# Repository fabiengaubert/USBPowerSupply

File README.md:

# USBPowerSupply

USB Power supply design for eurorack, works with powerbanks or good USB wallwarts

- 2 HP
- 500mA at +12v, 500mA at - 12v
- efficient isolated DC-DC switching regulators with low heat release
- surge voltage and over-current protection with resettable fuse
- reversed polarity protection
- common mode choke and multiple ferrite beads with PI filters for noise filtering
- 1 LED per rail to indicated overload and short circuits

Warning and reserves:
- the two DC-DC switching regulators are expensive compared to the rest of the components: they represent about 75% of the total cost, I will work on a cheaper version with at least the same performances in the future
- the minimum voltage allowed is 4.5v, which we know can be too much for USB chargers, as they are unregulated sources of voltage. when current rises above 0.5A, most of them drop the voltage below this value. There is a need to test chargers and advise specific ones. With power banks they should be no problems as their output is regulated

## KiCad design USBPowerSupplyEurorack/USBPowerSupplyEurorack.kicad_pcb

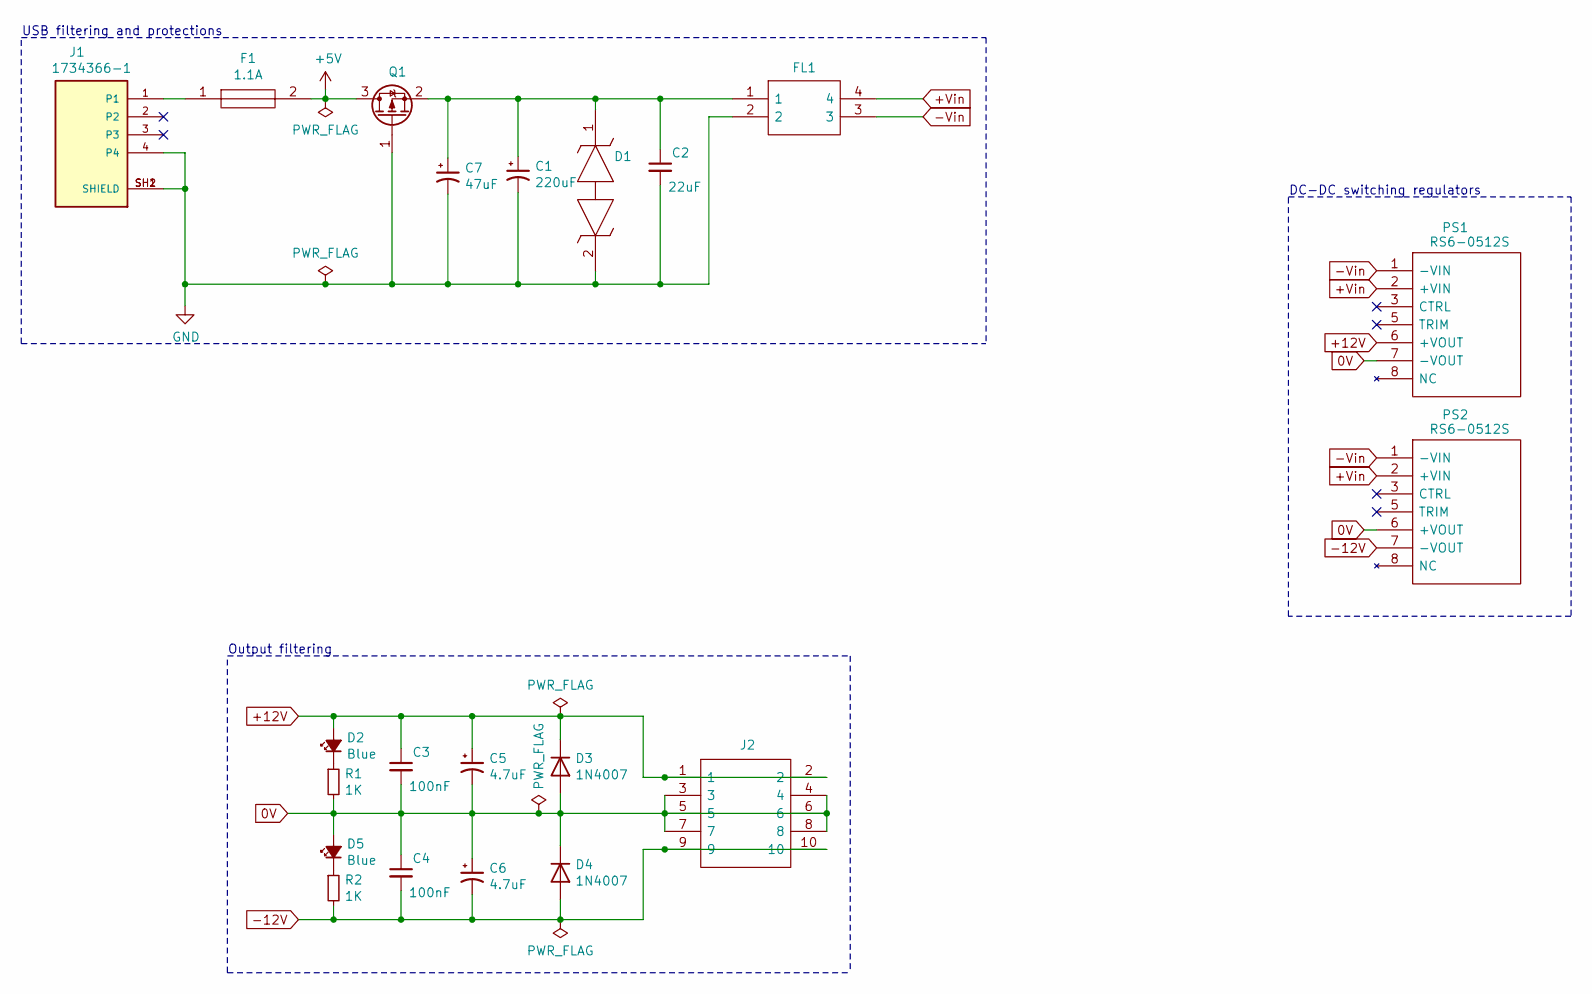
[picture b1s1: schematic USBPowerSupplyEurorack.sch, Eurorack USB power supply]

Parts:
C1: 220uF; C_Elec_6.3x7.7; LCSC C127327
C2: 22uF; C_0805_2012Metric; LCSC C45783
C3, C4: 100nF; C_0402_1005Metric; LCSC C1525
C5, C6: 4.7uF; C_Elec_4x5.4; LCSC C116398
C7: 47uF; C_Elec_5x5.4; LCSC C294514
D1: SMAJ5.0CA; DO-214AC-BIPOLAR; Manufacturer_Part_Number SMAJ5.0CA; Mouser Part Number 576-SMAJ5.0CA
D2, D5: Blue; LED_0603
D3, D4: 1N4007; D_SOD-123F; LCSC C64898
F1: 1.1A; Fuse_1812_4532Metric; Manufacturer_Part_Number 1812L110/16DR; Mouser Part Number 576-1812L110/16DR
FL1: ACP3225-102-2P-T000; ACP3225; Manufacturer_Part_Number ACP3225-102-2P-T000; Mouser Part Number 810-ACP32251022PT000
J1: 1734366-1; TE_1734366-1
J2: 95278-501A10LF; 95278501A10LF; Manufacturer_Part_Number 95278-501A10LF; Mouser Part Number 649-95278-501A10LF
PS1, PS2: RS6-0512S; RS60512S; Manufacturer_Part_Number RS6-0512S; Mouser Part Number 919-RS6-0512S
Q1: Q_PMOS_GSD; SOT-23-3; LCSC C15127
R1, R2: 1K; R_0805_2012Metric; LCSC C17513

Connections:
0V: C3.2, C4.1, C5.2, C6.1, D3.2 (A), D4.1 (K), D5.2 (A), J2.3, J2.4, J2.5, J2.6, J2.7, J2.8, PS1.7 (-VOUT), PS2.6 (+VOUT), R1.2
+5V: F1.2, Q1.3 (D)
+12V: C3.1, C5.1, D2.2 (A), D3.1 (K), J2.1, J2.2, PS1.6 (+VOUT)
+Vin: FL1.4, PS1.2 (+VIN), PS2.2 (+VIN)
-12V: C4.2, C6.2, D4.2 (A), J2.9, J2.10, PS2.7 (-VOUT), R2.2
-Vin: FL1.3, PS1.1 (-VIN), PS2.1 (-VIN)
GND: C1.2, C2.2, C7.2, D1.2, FL1.2, J1.4, J1.SH1 (SHIELD), J1.SH2 (SHIELD), Q1.1 (G)
unnamed: C1.1, C2.1, C7.1, D1.1, FL1.1, Q1.2 (S)
unnamed: D2.1 (K), R1.1
unnamed: D5.1 (K), R2.1
unnamed: F1.1, J1.1

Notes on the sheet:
USB filtering and protections
DC-DC switching regulators
Output filtering

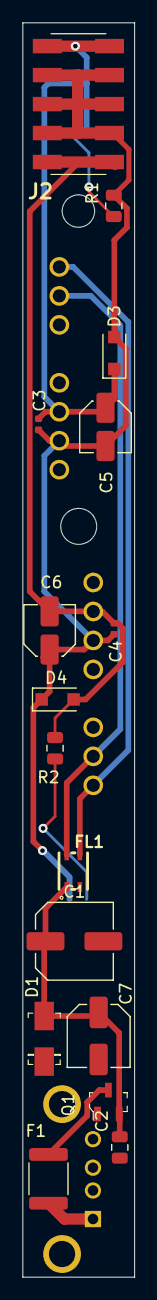
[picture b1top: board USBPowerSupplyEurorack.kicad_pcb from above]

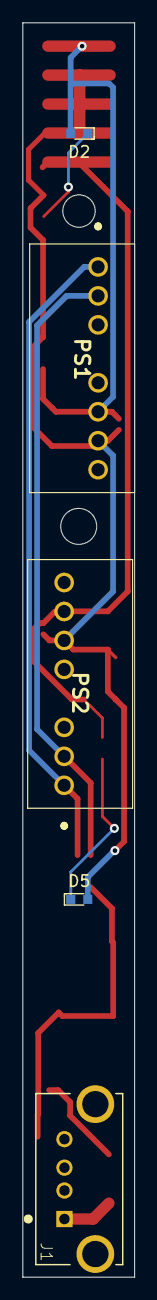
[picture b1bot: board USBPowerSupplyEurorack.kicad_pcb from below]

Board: 2 copper layers, 9.8 x 110.0 mm, 21 parts (5 on the bottom side), 11 nets.

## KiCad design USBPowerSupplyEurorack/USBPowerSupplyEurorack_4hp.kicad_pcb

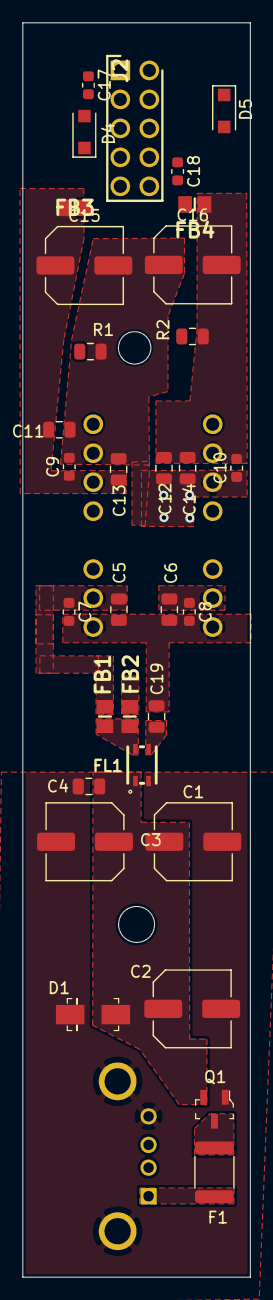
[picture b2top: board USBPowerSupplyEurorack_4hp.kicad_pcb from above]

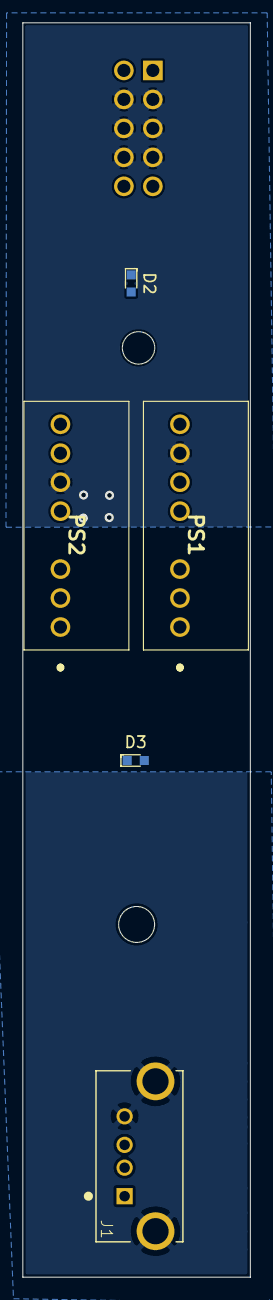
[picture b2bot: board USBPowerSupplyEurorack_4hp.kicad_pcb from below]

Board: 2 copper layers, 19.9 x 110.0 mm, 37 parts (5 on the bottom side), 16 nets, no tracks yet.

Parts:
C1, C15, C16: 47uF; C_Elec_6.3x5.4
C2, C3: 220uF; C_Elec_6.3x7.7
C4, C5, C6, C11, C12, C13, C14: 22uF; C_0805_2012Metric
C7, C8, C9, C10, C17, C18: 100nF; C_0603_1608Metric
C19: 10uF; C_0805_2012Metric
D1: SMAJ5.0CA; DO-214AC-BIPOLAR
D2, D3: Blue; LED_0603
D4, D5: 1N4007; D_SOD-123F
F1: 3A hold; Fuse_1812_4532Metric
FB1, FB2, FB3, FB4: C15957; BEADC2012X105N
FL1: ACP3225-102-2P-T000; ACP3225
J1: 1734366-1; TE_1734366-1
J2: 10129381-910001BLF; HDRV10W67P254_2X5_1270X483X858P
PS1, PS2: RS6-0512S; RS60512S
Q1: Q_PMOS_GSD; SOT-23-3
R1, R2: 1K; R_0805_2012Metric

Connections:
0V: C9.2, C10.1, C11.2, C12.1, C13.2, C14.1, C15.2, C16.1, C17.2, C18.1, D3.2, D4.2, D5.1, J2.3, J2.4, J2.5, J2.6, J2.7, J2.8, PS1.7, PS2.6, R1.2
+5V: F1.2, Q1.3
+12V: C9.1, C11.1, C13.1, C15.1, D2.2, FB3.2, PS1.6
+Vin1: C5.1, C7.1, FB1.1, PS1.2
+Vin2: C6.1, C8.1, FB2.1, PS2.2
-12V: C10.2, C12.2, C14.2, C16.2, FB4.2, PS2.7, R2.2
-Vin1: C5.2, C6.2, C7.2, C8.2, C19.2, PS1.1, PS2.1
GND: C1.2, C2.2, C3.2, C4.2, D1.2, FL1.2, J1.4, J1.SH1, J1.SH2, Q1.1
unnamed: C1.1, C2.1, C3.1, C4.1, D1.1, FL1.1, Q1.2
unnamed: C17.1, D4.1, FB3.1, J2.1, J2.2
unnamed: C18.2, D5.2, FB4.1, J2.9, J2.10
unnamed: C19.1, FL1.3
unnamed: D2.1, R1.1
unnamed: D3.1, R2.1
unnamed: F1.1, J1.1
unnamed: FB1.2, FB2.2, FL1.4

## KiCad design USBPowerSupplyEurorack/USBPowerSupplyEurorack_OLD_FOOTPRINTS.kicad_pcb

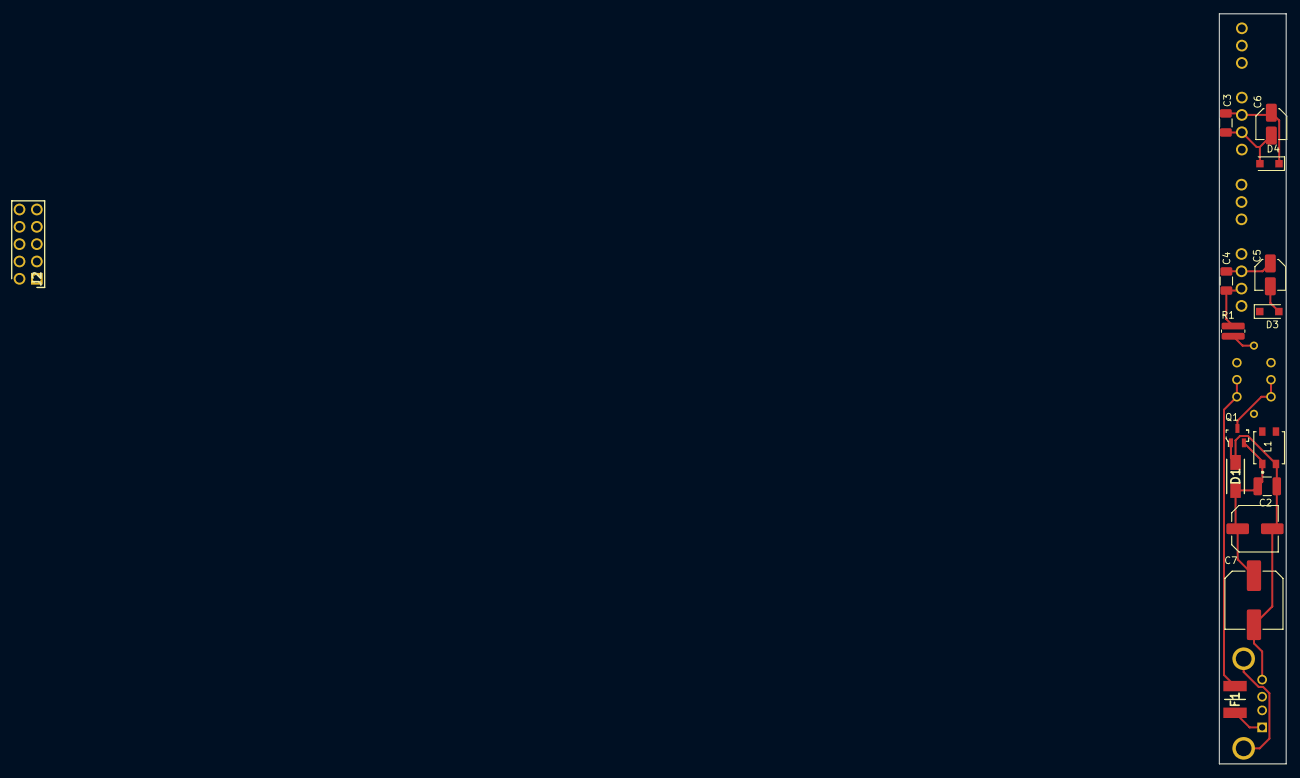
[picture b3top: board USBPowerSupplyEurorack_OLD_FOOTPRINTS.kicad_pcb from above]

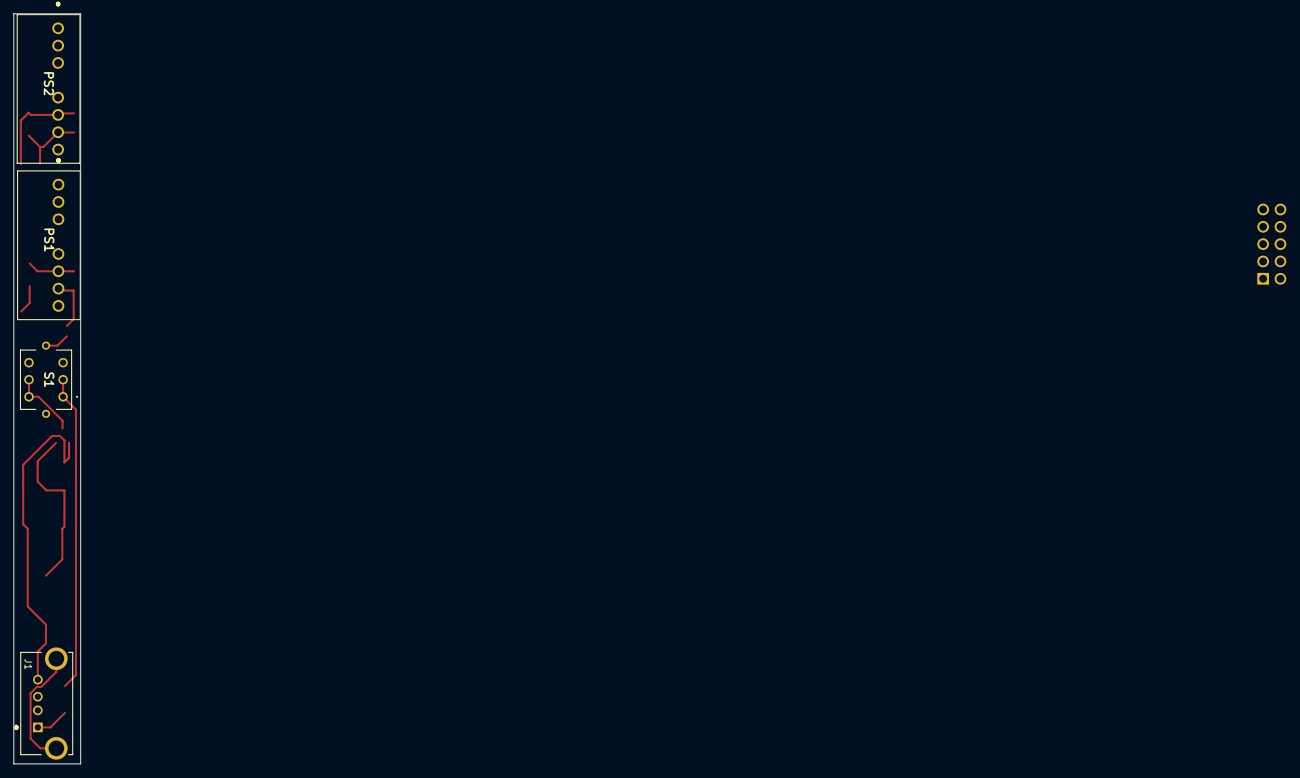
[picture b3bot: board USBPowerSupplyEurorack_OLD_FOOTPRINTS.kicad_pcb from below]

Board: 2 copper layers, 9.8 x 110.0 mm, 19 parts (4 on the bottom side), 12 nets.

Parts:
C1: 220uF; C_Elec_8x10.2
C2: 22uFMLCC; C_1210_3225Metric
C3, C4: 100nF MLCC; C_1206_3216Metric
C5, C6: 1uF; C_Elec_4x5.4
C7: 47uF; C_Elec_6.3x5.8
D1: SMAJ5.0CA; DIONM5026X229N
D3, D4: 1N4004; D_SOD-123F
F1: 1812L110; FUSC4632X125N
J1: 1734366-1; TE_1734366-1
J2: 10129381-910001BLF; HDRV10W67P254_2X5_1270X483X858P
L1: ACM4520V-901-2P-T; TDK-ACM4520V-901-2P-T-0
PS1, PS2: RS6-0512S; RS60512S
Q1: Q_PMOS_GSD; SOT-23-3
R1: 510; R_0612_1632Metric
S1: LP4OA1PBCTR

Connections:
0V: C3.1, C4.2, C5.2, C6.1, D3.2, D4.1, J2.3, J2.4, J2.5, J2.6, J2.7, J2.8, PS1.7, PS2.6, R1.2
+5V: Q1.3, S1.4, S1.5
+5VD: F1.2, S1.1, S1.2
+12V: C4.1, C5.1, D3.1, J2.1, J2.2, PS1.6, S1.L1
+Vin: L1.4, PS1.2, PS2.2
-12V: C3.2, C6.2, D4.2, J2.9, J2.10, PS2.7
-Vin: L1.3, PS1.1, PS2.1
GND: C1.2, C2.2, C7.2, D1.2, J1.4, L1.2, Q1.1
unnamed: C1.1, C2.1, C7.1, D1.1, L1.1, Q1.2
unnamed: F1.1, J1.1
unnamed: J1.SH1, J1.SH2
unnamed: R1.1, S1.L2

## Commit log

2020-12-21 created KiCAD project with basic components
2020-12-21 added component footprints and going forward on schematics
2020-12-21 added common choke and other components
2020-12-21 changed diode for lower forward voltage, prepared 2HP PCB contour
2020-12-22 completed schematics
2020-12-22 finished schematics, added PMOS for reversed polarity protection
2020-12-23 replaced dual regulator by two regulators for more current
2020-12-23 finished schematics
2020-12-24 replaced power plug with open one
2020-12-24 added footprints with LCSC components
2020-12-24 changed TVS symbol as footprint was not valid
2020-12-24 updated all footprints in pcbnew
2020-12-25 placed components on the PCB
2020-12-25 routing test for price evaluation
2020-12-26 connected switch to control the DC-DC converters
2020-12-28 changing footprints for JLC available parts
2020-12-28 finished updating footprints, edited TVS diode's footprint
2020-12-28 placed components, need to change power 2x5 for SMT
2020-12-28 replaced power header for SMT, finished placement
2020-12-28 worked a components placement
2020-12-29 simplified schematics
2020-12-30 added 3D models
2020-12-30 naive routing to try
2021-01-01 removed switch and simplified schematics, added a second LED for -12v
2021-01-03 changed footprints placement, added the two LEDs
2021-01-08 added LEDs, all components are placed now
2021-01-08 new naive routing
2021-01-09 final placement
2021-01-09 updated readme with explanations
2021-01-09 added 3D model
2021-01-09 resize image
2021-01-09 correct readme
2021-01-09 completed readme
2021-01-12 going to 4hp for better routing
2021-01-12 naive placement and routing
2021-01-12 changed caps on schematics, added PI filter and bigger caps as we have now 4HP
2021-01-12 updated footprints
2021-01-12 new components placement
2021-01-12 still testing routing
2021-01-13 changing placement of components
2021-01-18 resizing components for max 3A input current
2021-01-18 changed some components for matching current ratings
2021-01-20 finished updating condensators to the right voltage rating, updated BOM and footprints
2021-01-21 updated information in readme after schematics modifications multiple schematics modifications
2021-01-21 updated components and footprints
2021-01-26 moved holes for panel, updated power plug
2021-01-27 working on the routing, making copper pours
2021-03-11 changed mistake in schematics
